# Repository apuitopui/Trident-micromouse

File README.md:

# TRIDENT - Classic size micromouse
Trident is a robotic project to compete in [classic size micromouse](https://www.ntf.or.jp/). 

## Circuit

## Specification
|Specification|Value| 
|---|---|
|Size(W x L x H)| 70 x 84 x 30mm |
|Weight|About 100g|
|CPU|STM32F405RGT6|
|Battery|Tahmazo LP2S1P360RE|
|Motor|Faulhaber 1717T006SR|
|Encoder|IE2-256|
|Motor driver|TB6612FNG|
|Pinion|M0.5 9T Brass|
|Spur Gear|M0.5 42T PA12 MJF|
|Tire|Kyosho high grip tire|
|Gyro rensor|MPU9250|
|Wall sensor LED|SFH4500|
|Wall sensor Phototransistor| ST-1KL3A|

## Environment 
* IDE : STM32 Cube IDE
* EDA : Autodesk Eagle
* CAD : Autodesk Fusion

## Joined micromouse competition
|Date|Competition|Best time|Rank|
|---|---|---|---|
|2023/02/19|第43回全日本マイクロマウス大会|0:18.822|7|
|2023/09/24|第４０回マイクロマウス北陸信越地区大会|0:11.231|5|
|2023/11/12|第３９回マイクロマウス東日本地区大会|0:10.233|8|
|2023/12/09|第３７回全日本学生マイクロマウス大会|0:08.502|8|
|2023/02/18|第44回全日本マイクロマウス大会|0:09.356|14|

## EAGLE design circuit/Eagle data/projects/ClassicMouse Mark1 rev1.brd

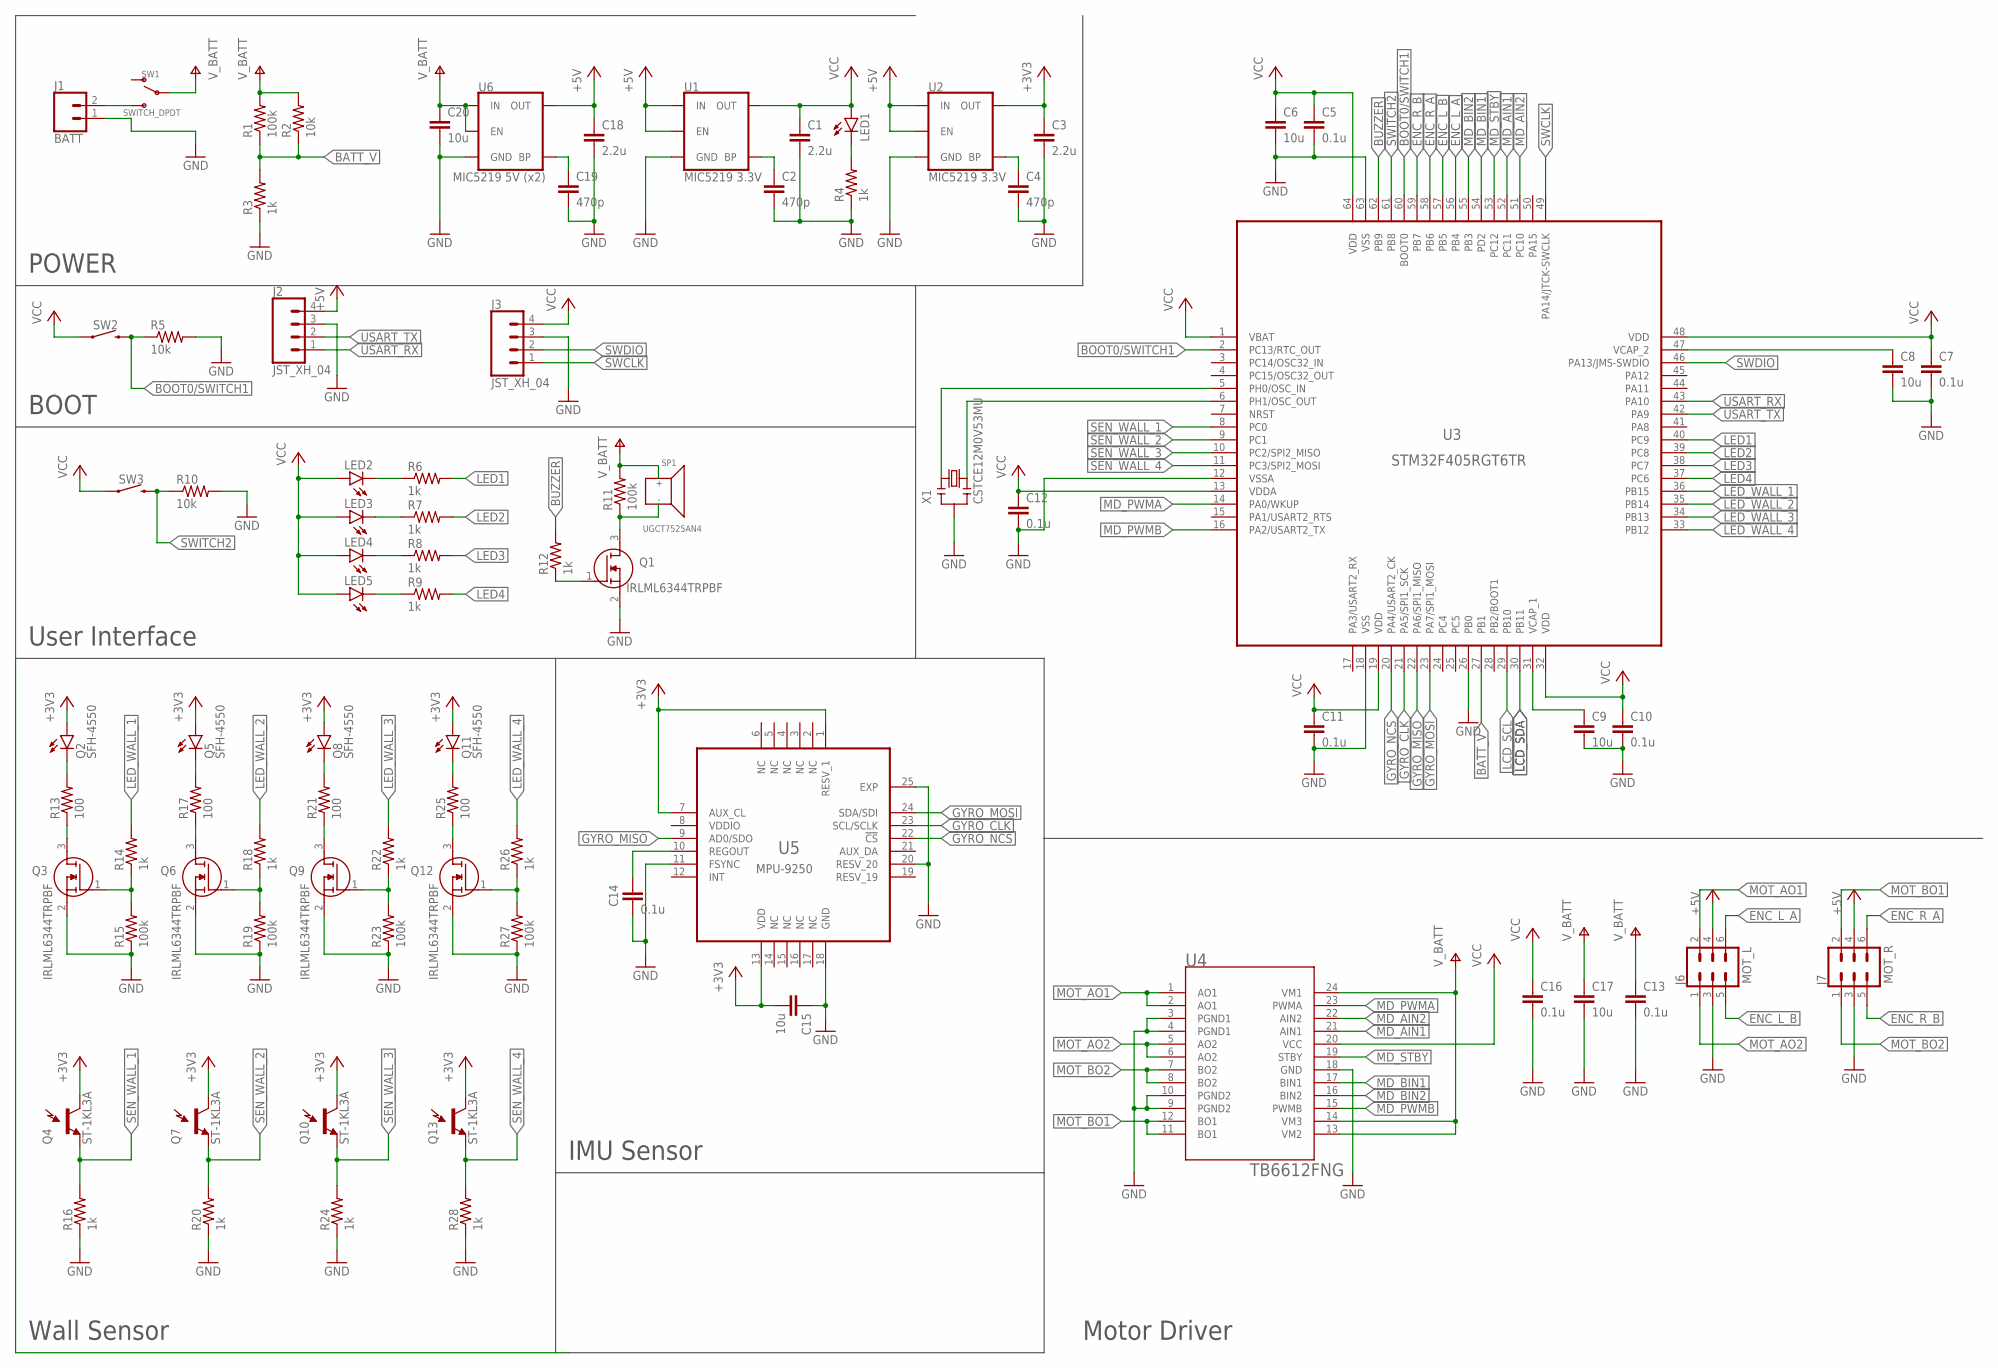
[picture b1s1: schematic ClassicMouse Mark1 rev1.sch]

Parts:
C1, C3, C18: 2.2u; C0603K
C2, C4, C19: 470p; C0603K
C5, C7, C10, C11, C12, C13, C14, C16: 0.1u; C0603K
C6, C8, C9: 10u; C0603K
C15, C17, C20: 10u; C1206
J1: BATT; JST-XH-02-PACKAGE-ROUND-PAD
J2, J3: JST_XH_04; JST-XH-04-PACKAGE-ROUND-PAD
J6: MOT_L; 2X3-NS
J7: MOT_R; 2X3-NS
LED1, LED2, LED3, LED4, LED5: LEDCHIPLED_0603; CHIPLED_0603
Q1, Q3, Q6, Q9, Q12: IRLML6344TRPBF; SOT95P260X110-3N
Q2, Q5, Q8, Q11: SFH-4550; CONN_02
Q4, Q7, Q10, Q13: ST-1KL3A; CONN_02
R1, R11, R15, R19, R23, R27: 100k; R0603
R2, R5, R10: 10k; R0603
R3, R4, R6, R7, R8, R9, R12, R14, R16, R18, R20, R22, R24, R26, R28: 1k; R0603
R13, R17, R21, R25: 100; R0603
SP1: UGCT7525AN4
SW1: SWITCH_DPDT
SW2, SW3: MOMENTARY-SWITCH-SPST-SMD-4.6X2.8MM; TACTILE_SWITCH_SMD_4.6X2.8MM
U1, U2: MIC5219 3.3V; SOT23-5
U3: STM32F405RGT6TR; QFP50P1200X1200X160-64N
U4: TB6612FNG; SOP65P760X160-24N
U5: MPU-9250; QFN40P300X300X105-25N
U6: MIC5219 5V (x2); SOT23-5
X1: CSTCE12M0V53MU; CSTCE12M0V53

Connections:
+3V3: C3.1, C15.2, Q2.+ (A), Q4.+ (C1), Q5.+ (A), Q7.+ (C1), Q8.+ (A), Q10.+ (C1), Q11.+ (A), Q13.+ (C1), U2.5 (OUT), U5.1 (RESV_1), U5.7 (AUX_CL), U5.13 (VDD)
+5V: C18.1, J2.4, J6.4, J7.4, U1.1 (IN), U1.3 (EN), U2.1 (IN), U2.3 (EN), U6.5 (OUT)
BATT_V: R1.1, R2.1, R3.2, U3.27 (PB1)
BOOT0/SWITCH1: R5.1, SW2.3 (2), SW2.4 (2), U3.2 (PC13/RTC_OUT), U3.60 (BOOT0)
BUZZER: R12.2, U3.62 (PB9)
ENC_L_A: J6.6, U3.56 (PB4)
ENC_L_B: J6.5, U3.57 (PB5)
ENC_R_A: J7.6, U3.58 (PB6)
ENC_R_B: J7.5, U3.59 (PB7)
GND: C1.2, C2.2, C3.2, C4.2, C5.2, C6.2, C7.2, C8.2, C9.2, C10.2, C11.2, C12.2, C13.2, C14.2, C15.1, C16.2, C17.2, C18.2, C19.2, C20.2, J1.1, J2.3, J3.3, J6.3, J7.3, Q1.2 (S), Q3.2 (S), Q6.2 (S), Q9.2 (S), Q12.2 (S), R3.1, R4.1, R5.2, R10.2, R15.1, R16.1, R19.1, R20.1, R23.1, R24.1, R27.1, R28.1, U1.2 (GND), U2.2 (GND), U3.12 (VSSA), U3.18 (VSS), U3.26 (PB0), U3.63 (VSS), U4.3 (PGND1), U4.4 (PGND1), U4.9 (PGND2), U4.10 (PGND2), U4.18 (GND), U5.11 (FSYNC), U5.18 (GND), U5.20 (RESV_20), U5.25 (EXP), U6.2 (GND), X1.2
GYRO_CLK: U3.21 (PA5/SPI1_SCK), U5.23 (SCL/SCLK)
GYRO_MISO: U3.22 (PA6/SPI1_MISO), U5.9 (AD0/SDO)
GYRO_MOSI: U3.23 (PA7/SPI1_MOSI), U5.24 (SDA/SDI)
GYRO_NCS: U3.20 (PA4/USART2_CK), U5.22 (!CS)
LCD_SCL: U3.29 (PB10)
LCD_SDA: U3.30 (PB11)
LED1: R6.2, U3.40 (PC9)
LED2: R7.2, U3.39 (PC8)
LED3: R8.2, U3.38 (PC7)
LED4: R9.2, U3.37 (PC6)
LED_WALL_1: R14.2, U3.36 (PB15)
LED_WALL_2: R18.2, U3.35 (PB14)
LED_WALL_3: R22.2, U3.34 (PB13)
LED_WALL_4: R26.2, U3.33 (PB12)
MD_AIN1: U3.52 (PC11), U4.21 (AIN1)
MD_AIN2: U3.51 (PC10), U4.22 (AIN2)
MD_BIN1: U3.54 (PD2), U4.17 (BIN1)
MD_BIN2: U3.55 (PB3), U4.16 (BIN2)
MD_PWMA: U3.14 (PA0/WKUP), U4.23 (PWMA)
MD_PWMB: U3.16 (PA2/USART2_TX), U4.15 (PWMB)
MD_STBY: U3.53 (PC12), U4.19 (STBY)
MOT_AO1: J6.2, U4.1 (AO1), U4.2 (AO1)
MOT_AO2: J6.1, U4.5 (AO2), U4.6 (AO2)
MOT_BO1: J7.2, U4.11 (BO1), U4.12 (BO1)
MOT_BO2: J7.1, U4.7 (BO2), U4.8 (BO2)
unnamed: J1.2, SW1.3 (S), SW1.6 (S)
unnamed: C2.1, U1.4 (BP)
unnamed: U3.6 (PH1/OSC_OUT), X1.3
unnamed: C4.1, U2.4 (BP)
unnamed: U3.5 (PH0/OSC_IN), X1.1
unnamed: C8.1, U3.47 (VCAP_2)
unnamed: C9.1, U3.31 (VCAP_1)
unnamed: LED1.C, R4.2
unnamed: Q1.3 (D), R11.1, SP1.2 (GND)
unnamed: Q1.1 (G), R12.1
unnamed: Q2.- (C), R13.2
unnamed: Q3.3 (D), R13.1
unnamed: Q5.- (C), R17.2
unnamed: Q3.1 (G), R14.1, R15.2
unnamed: Q6.3 (D), R17.1
unnamed: Q6.1 (G), R18.1, R19.2
unnamed: Q8.- (C), R21.2
unnamed: Q9.3 (D), R21.1
unnamed: Q9.1 (G), R22.1, R23.2
unnamed: Q11.- (C), R25.2
unnamed: Q12.3 (D), R25.1
unnamed: Q12.1 (G), R26.1, R27.2
unnamed: LED2.C, R6.1
unnamed: LED3.C, R7.1
unnamed: C14.1, U5.10 (REGOUT)
unnamed: C19.1, U6.4 (BP)
unnamed: LED4.C, R8.1
unnamed: LED5.C, R9.1
SEN_WALL_1: Q4.- (E1), R16.2, U3.8 (PC0)
SEN_WALL_2: Q7.- (E1), R20.2, U3.9 (PC1)
SEN_WALL_3: Q10.- (E1), R24.2, U3.10 (PC2/SPI2_MISO)
SEN_WALL_4: Q13.- (E1), R28.2, U3.11 (PC3/SPI2_MOSI)
SWCLK: J3.1, U3.49 (PA14/JTCK-SWCLK)
SWDIO: J3.2, U3.46 (PA13/JMS-SWDIO)
SWITCH2: R10.1, SW3.3 (2), SW3.4 (2), U3.61 (PB8)
USART_RX: J2.1, U3.43 (PA10)
USART_TX: J2.2, U3.42 (PA9)
V+: C13.1, C17.1, C20.1, R1.2, R2.2, R11.2, SP1.1 (V), SW1.2, SW1.5, U4.13 (VM2), U4.14 (VM3), U4.24 (VM1), U6.1 (IN), U6.3 (EN)
VCC: C1.1, C5.1, C6.1, C7.1, C10.1, C11.1, C12.1, C16.1, J3.4, LED1.A, LED2.A, LED3.A, LED4.A, LED5.A, SW2.1, SW2.2 (1), SW3.1, SW3.2 (1), U1.5 (OUT), U3.1 (VBAT), U3.13 (VDDA), U3.19 (VDD), U3.32 (VDD), U3.48 (VDD), U3.64 (VDD), U4.20 (VCC)
VDDIO: U5.8 (VDDIO)

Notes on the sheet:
POWER
BOOT
User Interface
Wall Sensor
IMU Sensor
Motor Driver

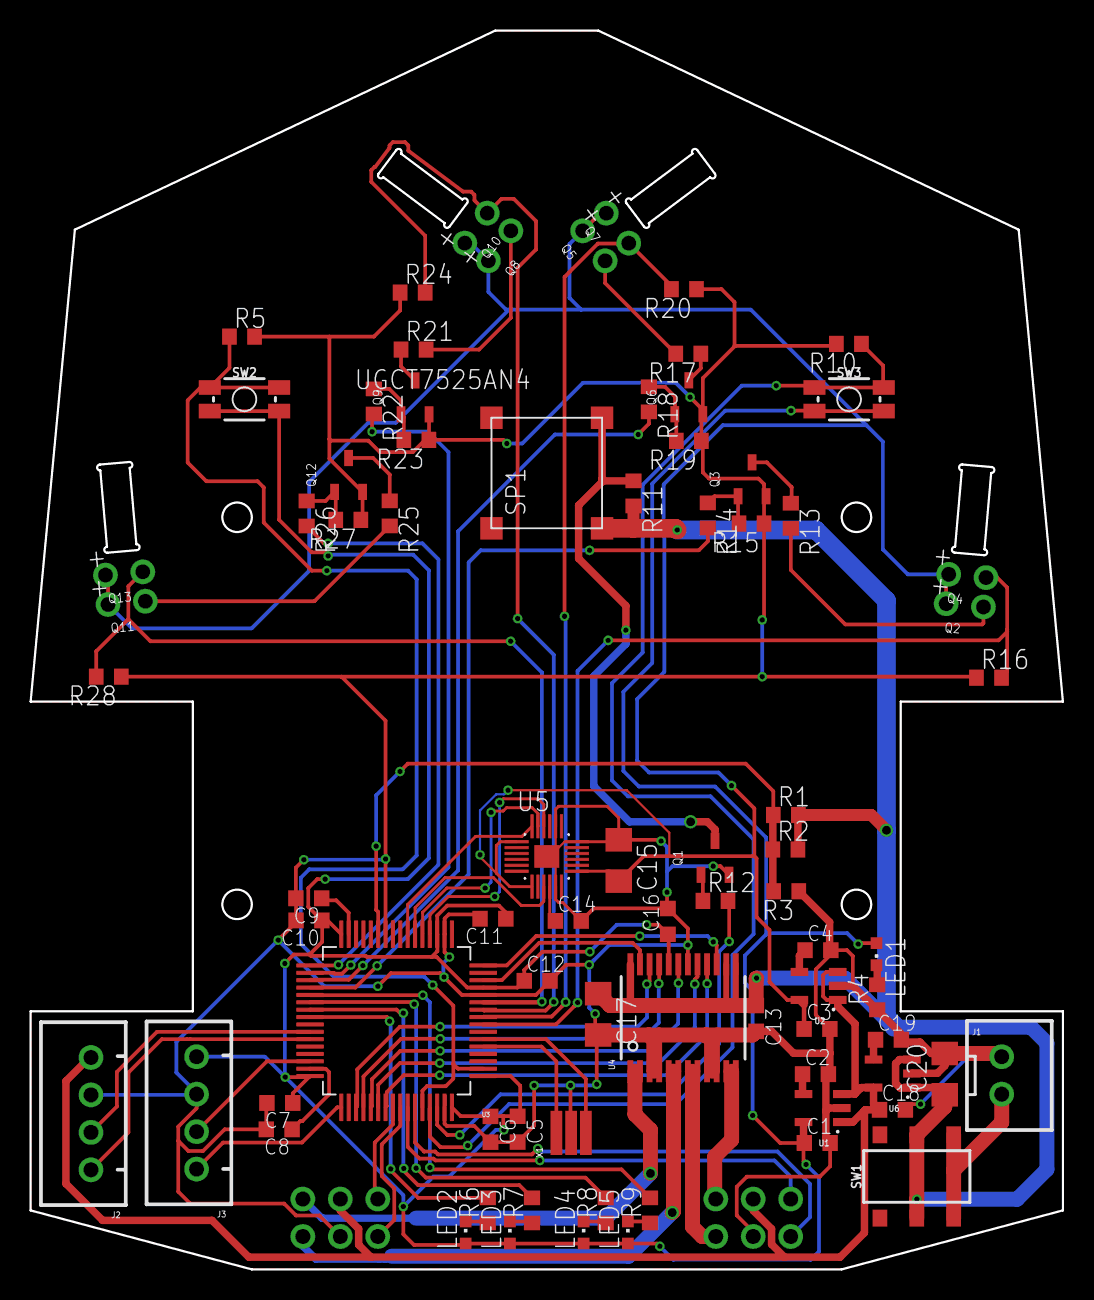
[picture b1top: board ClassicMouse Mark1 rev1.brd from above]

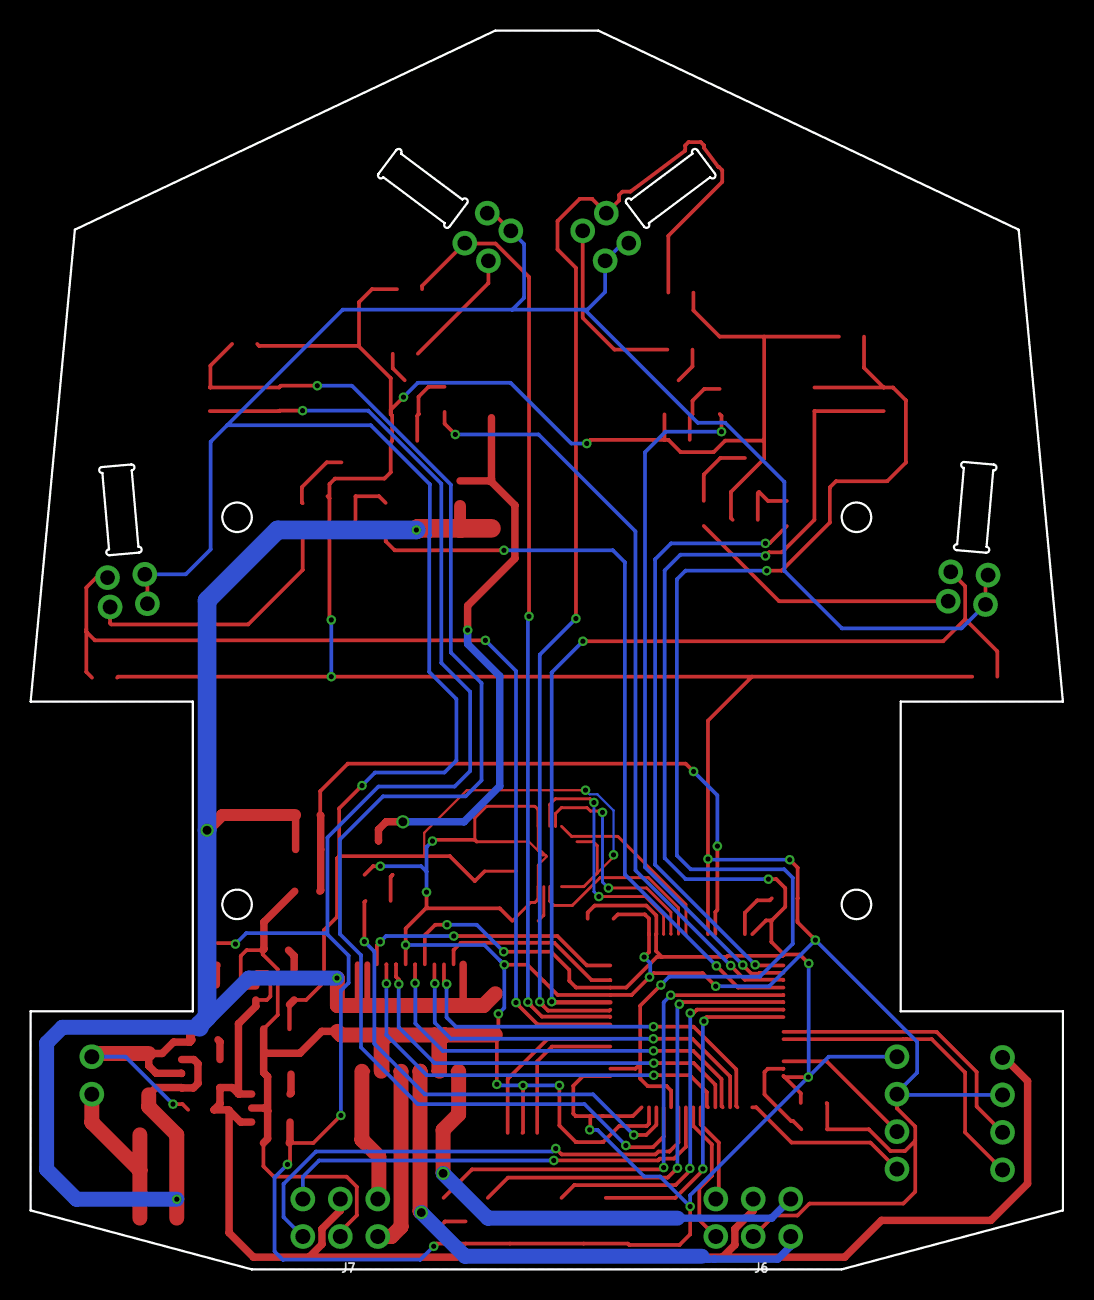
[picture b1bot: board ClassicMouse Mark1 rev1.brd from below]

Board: 2 copper layers, 70.0 x 84.0 mm, 82 parts (2 on the bottom side), 72 nets.

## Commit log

2024-09-20 Fix image in README
2024-09-20 Changes in README
